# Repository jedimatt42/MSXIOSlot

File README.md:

# MSXIOSlot

PCBoard design for an MSX expansion slot adapter to 1 full expansion slot + 1 
IO Slot. 

This repository contains KiCad design files based on the diagrams and 
information provided here:

[Hans Otten 2002/2005](http://msx.hansotten.com/do-it-yourself/memory-mappers-slots/slot-extender/)

## What

This is a simple IO Slot extender. It allows the forward slow to receive the 
MSX slot select, and the rear slot to always see high signal (off) for slot 
select. This does not perform subslot decoding. The second slot is only able 
to support IO port based expansions, like the V9990 PowerGraph Lite. 

This differes from Mr. Otten's work in that it does not include a disable 
switch on the slot select line. 

## Success

This has been tested on my Panasonic FS-A1FX MSX2+ system with GR8NET and 
V9990 PowerGraph Lite connected with this adapter. 

### Almost but not quite...

It turned out that the width of the edge card was too narrow, allowing the 
adapter to be inserted into the MSX askew such that it wouldn't work. 

The KiCad design has been updated! That should solve the problem. 

For the pcboards that I've already had printed, there is an edgecard-sliver 
model file in STL format that can be printed at 1:1mm scale. 2 of these could 
be 3D printed and 1 glued to each end of the edge card to guide it into the 
correct centering of the MSX cartridge slot.

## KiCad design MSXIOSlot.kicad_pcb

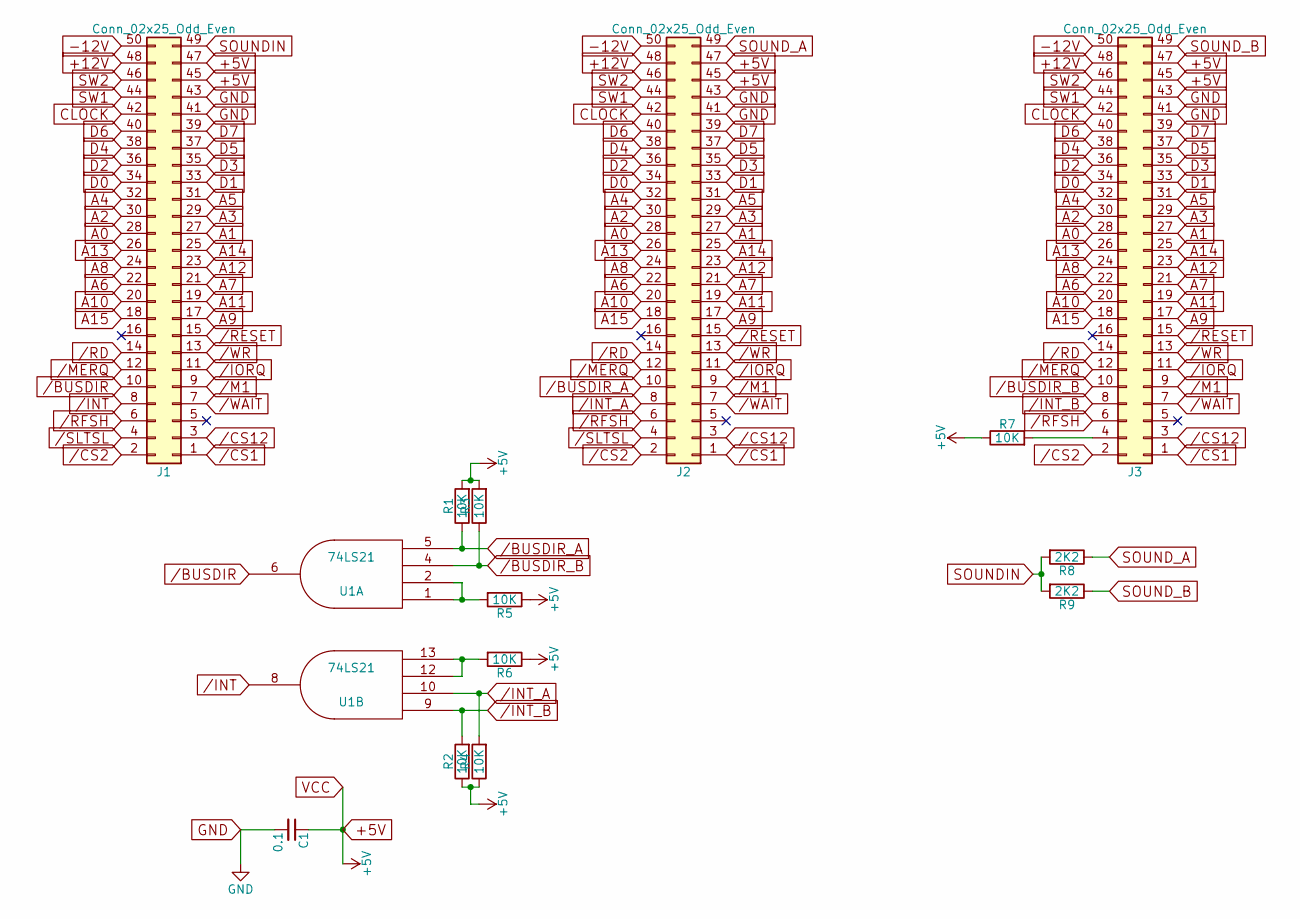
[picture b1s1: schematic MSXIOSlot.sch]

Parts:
C1: 0.1; C_Disc_D4.7mm_W2.5mm_P5.00mm
J1: Conn_02x25_Odd_Even; msx_cart_edge
J2, J3: Conn_02x25_Odd_Even; 50_pin_edge_female
R1, R2, R3, R4, R5, R6, R7: 10K; R_Axial_DIN0207_L6.3mm_D2.5mm_P7.62mm_Horizontal
R8, R9: 2K2; R_Axial_DIN0207_L6.3mm_D2.5mm_P7.62mm_Horizontal
U1: 74LS21; DIP-14_W7.62mm

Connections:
+5V: C1.1, J1.45, J1.47, J2.45, J2.47, J3.45, J3.47, R1.2, R2.1, R3.2, R4.1, R5.1, R6.1, R7.1, U1.14 (VCC)
+12V: J1.48, J2.48, J3.48
-12V: J1.50, J2.50, J3.50
/BUSDIR: J1.10, U1.6
/BUSDIR_A: J2.10, R1.1, U1.5
/BUSDIR_B: J3.10, R3.1, U1.4
/CS1: J1.1, J2.1, J3.1
/CS2: J1.2, J2.2, J3.2
/CS12: J1.3, J2.3, J3.3
/INT: J1.8, U1.8
/INT_A: J2.8, R4.2, U1.10
/INT_B: J3.8, R2.2, U1.9
/IORQ: J1.11, J2.11, J3.11
/M1: J1.9, J2.9, J3.9
/MERQ: J1.12, J2.12, J3.12
/RD: J1.14, J2.14, J3.14
/RESET: J1.15, J2.15, J3.15
/RFSH: J1.6, J2.6, J3.6
/SLTSL: J1.4, J2.4
/WAIT: J1.7, J2.7, J3.7
/WR: J1.13, J2.13, J3.13
A0: J1.28, J2.28, J3.28
A1: J1.27, J2.27, J3.27
A2: J1.30, J2.30, J3.30
A3: J1.29, J2.29, J3.29
A4: J1.32, J2.32, J3.32
A5: J1.31, J2.31, J3.31
A6: J1.22, J2.22, J3.22
A7: J1.21, J2.21, J3.21
A8: J1.24, J2.24, J3.24
A9: J1.17, J2.17, J3.17
A10: J1.20, J2.20, J3.20
A11: J1.19, J2.19, J3.19
A12: J1.23, J2.23, J3.23
A13: J1.26, J2.26, J3.26
A14: J1.25, J2.25, J3.25
A15: J1.18, J2.18, J3.18
CLOCK: J1.42, J2.42, J3.42
D0: J1.34, J2.34, J3.34
D1: J1.33, J2.33, J3.33
D2: J1.36, J2.36, J3.36
D3: J1.35, J2.35, J3.35
D4: J1.38, J2.38, J3.38
D5: J1.37, J2.37, J3.37
D6: J1.40, J2.40, J3.40
D7: J1.39, J2.39, J3.39
GND: C1.2, J1.41, J1.43, J2.41, J2.43, J3.41, J3.43, U1.7 (GND)
unnamed: J3.4, R7.2
unnamed: R5.2, U1.1, U1.2
unnamed: R6.2, U1.12, U1.13
SOUNDIN: J1.49, R8.2, R9.2
SOUND_A: J2.49, R8.1
SOUND_B: J3.49, R9.1
SW1: J1.44, J2.44, J3.44
SW2: J1.46, J2.46, J3.46

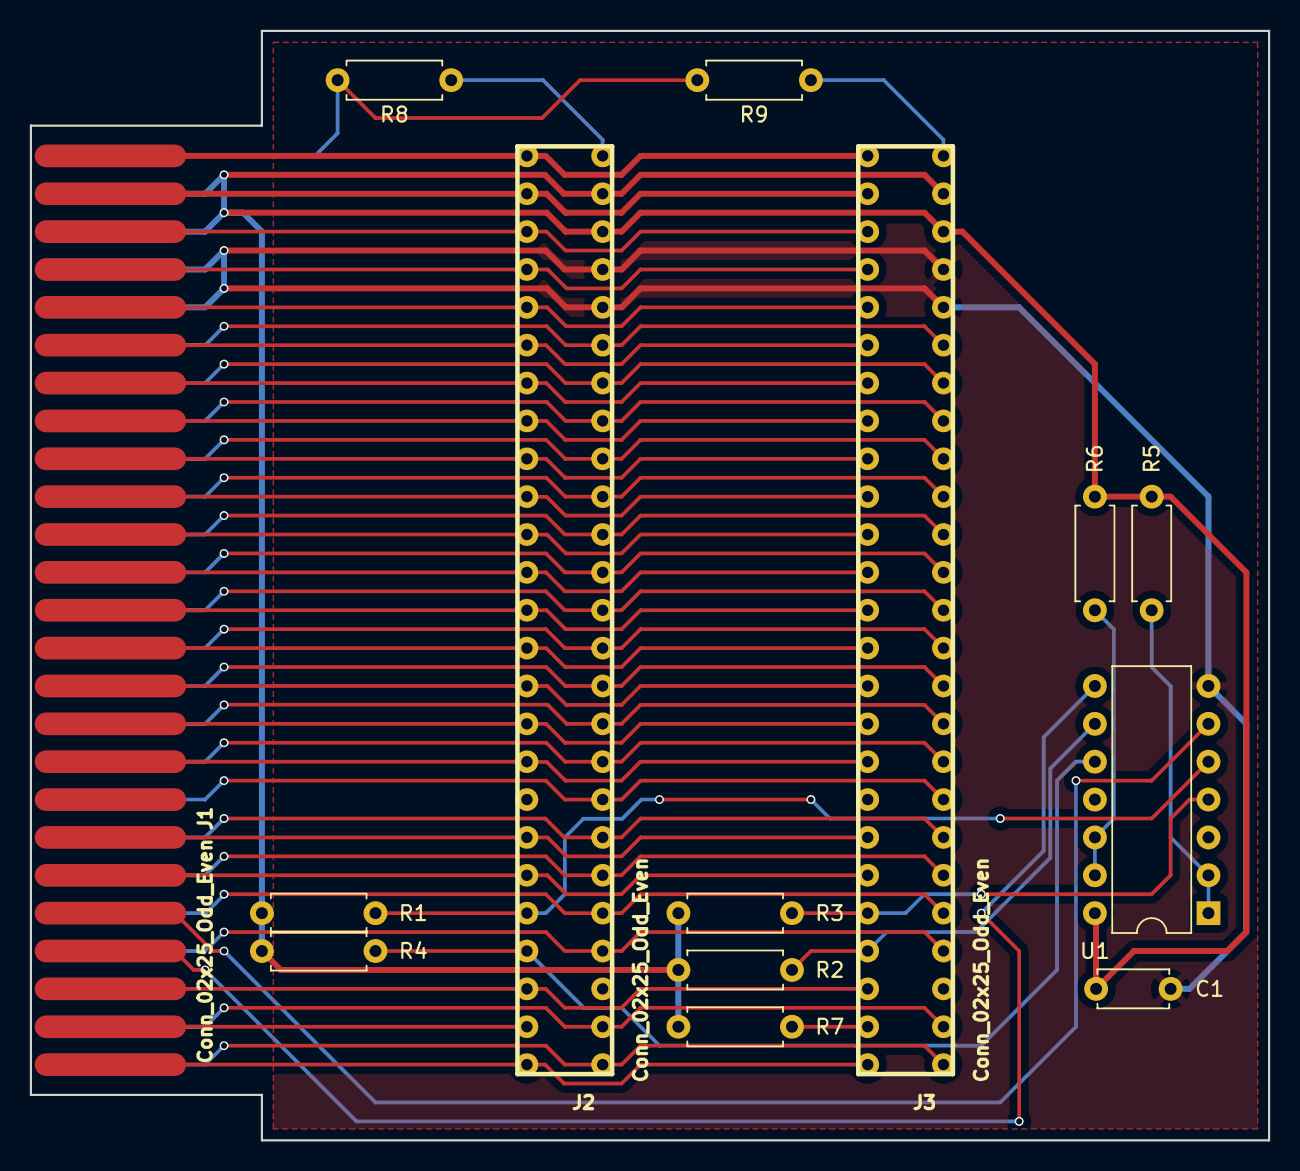
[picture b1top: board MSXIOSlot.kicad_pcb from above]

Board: 2 copper layers, 83.1 x 74.4 mm, 14 parts (0 on the bottom side), 55 nets.

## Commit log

2018-03-03 Updated! device has been tested.
2018-03-16 move audio resisters for better connector clearance
2018-03-17 slightly increase width of card edge to better center in MSX
2018-03-18 3D print model to help fix issue with preview design file.
2018-03-18 probably a user setting...
2018-03-18 oops, forgot pcboard thickness for this
